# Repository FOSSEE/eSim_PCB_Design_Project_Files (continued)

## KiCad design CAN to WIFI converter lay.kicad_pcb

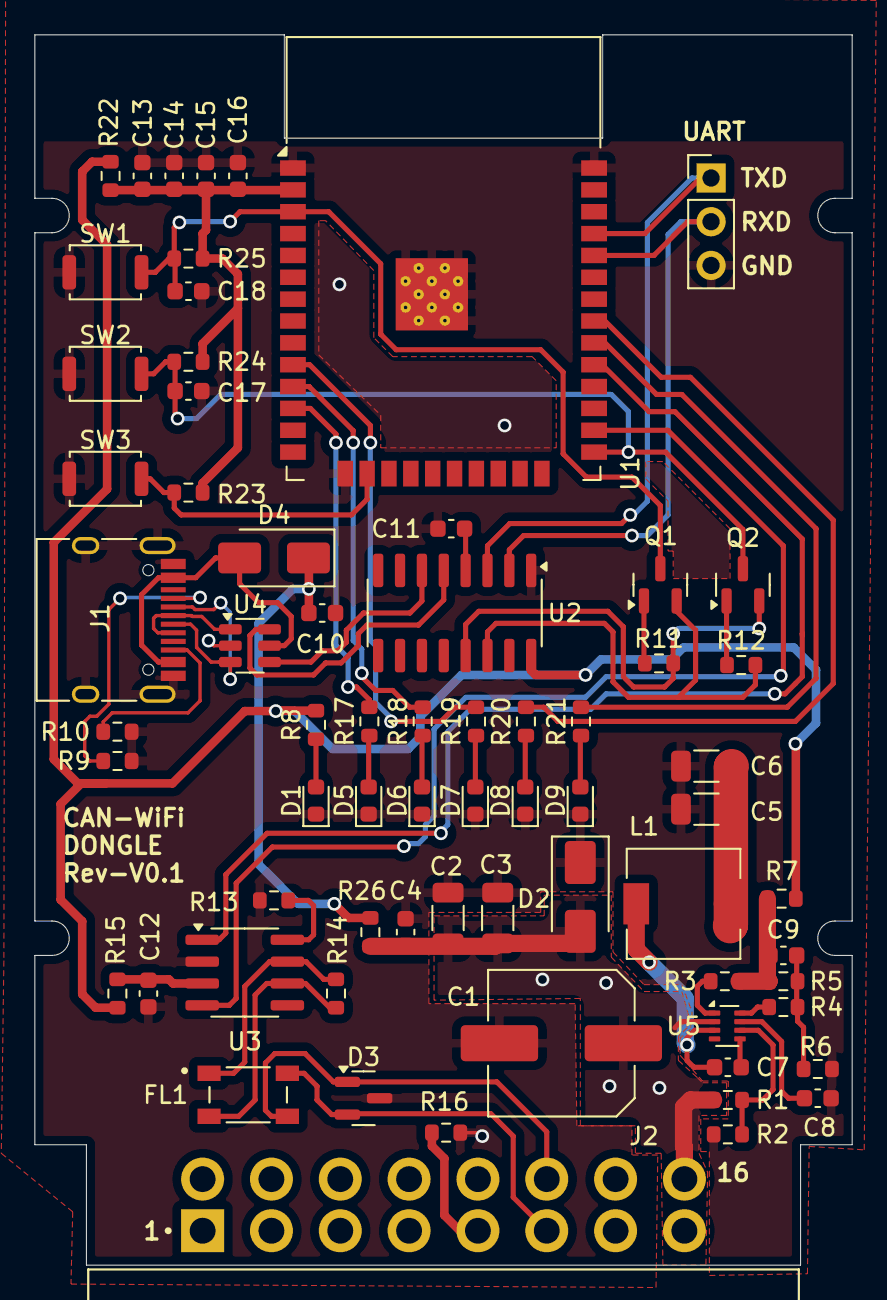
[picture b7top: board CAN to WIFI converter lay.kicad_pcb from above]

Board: 2 copper layers, 47.5 x 71.5 mm, 68 parts (0 on the bottom side), 51 nets.

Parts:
C1: 220uF; C_Elec_8x10.2
C2, C3: 10uF; C_1206_3216Metric
C4, C7, C12, C13, C14, C15, C16, C17, C18: 0.1uF; C_0603_1608Metric
C5, C6: 22uF; C_1206_3216Metric
C8: 22nF; C_0603_1608Metric
C9: 470pF; C_0603_1608Metric
C10: 10uF; C_0603_1608Metric
C11: 10nF; C_0603_1608Metric
D1, D5, D6, D7, D8, D9: LED; LED_0603_1608Metric
D2: SMAJ15CA; D_SMA
D3: SZNUP2105L; SOT-23
D4: SS14; D_SMA
FL1: ACT45B-510-2P-TL003; FIL_ACT45B-510-2P-TL003
J1: USB_C_Receptacle_USB2.0_16P; USB_C_Receptacle_HRO_TYPE-C-31-M-12
J2: C-OBD-II-16M; COMTECH_C-OBD-II-16M
J3: Conn_01x03_Pin; PinHeader_1x03_P2.54mm_Vertical
L1: 6.8uH; L_6.3x6.3_H3
Q1, Q2: SS8050; SOT-23
R1: 191K; R_0603_1608Metric
R2: 49.9K; R_0603_1608Metric
R3: 100K; R_0603_1608Metric
R4, R11, R12, R23, R24, R25: 10K; R_0603_1608Metric
R5: 51K; R_0603_1608Metric
R6: 9.09K; R_0603_1608Metric
R7, R15, R16, R22, R26: 0E; R_0603_1608Metric
R8, R17, R18, R19, R20, R21: 1K; R_0603_1608Metric
R9, R10: 5.1K; R_0603_1608Metric
R13: 2.4K; R_0603_1608Metric
R14: 120E; R_0603_1608Metric
SW1, SW2, SW3: SW_Push; SW_Push_SPST_NO_Alps_SKRK
U1: ESP32-WROOM-32
U2: CH340C; SOIC-16_3.9x9.9mm_P1.27mm
U3: SN65HVD230; SOIC-8_3.9x4.9mm_P1.27mm
U4: USBLC6-4SC6; SOT-23-6
U5: MP2338GTL-P; SOT-583-8

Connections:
5V: C10.1, D4.1 (K), R26.1
+3.3V: R7.1, R8.2, R15.2, R22.2, U2.16 (VCC)
BT/LED/IO25: R19.2, U1.10 (IO25)
CAN_3V3: C12.1, R15.1, U3.3 (VCC)
CAN_H: D3.2 (K), FL1.4, J2.6
CAN_L: D3.1 (K), FL1.3, J2.14
CAN_RX: U1.26 (IO4), U3.4 (R)
CAN_TX: U1.29 (IO5), U3.1 (D)
COMM/LED/IO18: R21.2, U1.30 (IO18)
D+: U2.5 (UD+), U4.6 (I/O4)
D-: U2.6 (UD-), U4.4 (I/O3)
DTR: Q2.2 (E), R11.2, U2.13 (~DTR)
EN: C18.2, Q1.3 (C), R25.1, SW1.2, U1.3 (EN)
ESP_3V3: C13.1, C14.1, C15.1, C16.1, R22.1, R23.2, R24.2, R25.2, U1.2 (VDD)
EXTRA/LED/IO19: R20.2, U1.31 (IO19)
EXT_GND: J2.5, R16.2
FAULT/LED/IO27: R17.2, U1.12 (IO27)
GND: C1.2, C2.2, C3.2, C4.2, C5.2, C6.2, C8.2, C10.2, C11.1, C12.2, C13.2, C14.2, C15.2, C16.2, C17.1, C18.1, D1.1 (K), D2.1 (A1), D3.3 (A), D5.1 (K), D6.1 (K), D7.1 (K), D8.1 (K), D9.1 (K), J1.A1 (GND), J1.A12 (GND), J1.B1 (GND), J1.B12 (GND), J1.S1 (SHIELD), J3.3, R2.2, R6.1, R9.1, R10.1, R13.2, R16.1, SW1.1, SW2.1, SW3.1, U1.1 (GND), U1.15 (GND), U1.38 (GND), U1.39 (GND), U2.1 (GND), U3.2 (GND), U4.2 (GND), U5.4 (GND)
IO0: C17.2, Q2.3 (C), R24.1, SW2.2, U1.25 (IO0)
unnamed: C5.1, C6.1, L1.2
unnamed: C9.2, R4.2, R5.1, R6.2
unnamed: D1.2 (A), R8.1
unnamed: D5.2 (A), R17.1
unnamed: D6.2 (A), R18.1
unnamed: D7.2 (A), R19.1
unnamed: D8.2 (A), R20.1
unnamed: D9.2 (A), R21.1
unnamed: J1.A5 (CC1), R9.2
unnamed: J1.B5 (CC2), R10.2
unnamed: Q1.1 (B), R11.1
unnamed: Q2.1 (B), R12.1
unnamed: C11.2, U2.4 (V3)
unnamed: FL1.1, R14.1, U3.7 (CANH)
unnamed: FL1.2, R14.2, U3.6 (CANL)
unnamed: R13.1, U3.8 (Rs)
unnamed: C7.2, U5.5 (BST)
unnamed: R4.1, U5.8 (FB)
unnamed: R3.2, U5.1 (PG)
unnamed: C8.1, U5.7 (SS)
unnamed: C7.1, L1.1, U5.3 (SW)
P_EN: R1.2, R2.1, U5.6 (EN)
RTS: Q1.2 (E), R12.2, U2.14 (~RTS)
RXD: J3.2, U1.34 (RXD0/IO3), U2.2 (TXD)
SW1/IO13: R23.1, SW3.2, U1.16 (IO13)
TXD: J3.1, U1.35 (TXD0/IO1), U2.3 (RXD)
USB_D+: J1.A6 (D+), J1.B6 (D+), U4.1 (I/O1)
USB_D-: J1.A7 (D-), J1.B7 (D-), U4.3 (I/O2)
VOUT: C9.1, R3.1, R5.2, R7.2
V_BATT: C1.1, C2.1, C3.1, C4.1, D2.2 (A2), J2.16, R1.1, R26.2, U5.2 (VIN)
V_BUS: D4.2 (A), J1.A4 (VBUS), J1.A9 (VBUS), J1.B4 (VBUS), J1.B9 (VBUS), U4.5 (VBUS)
WIFI/LED/IO26: R18.2, U1.11 (IO26)

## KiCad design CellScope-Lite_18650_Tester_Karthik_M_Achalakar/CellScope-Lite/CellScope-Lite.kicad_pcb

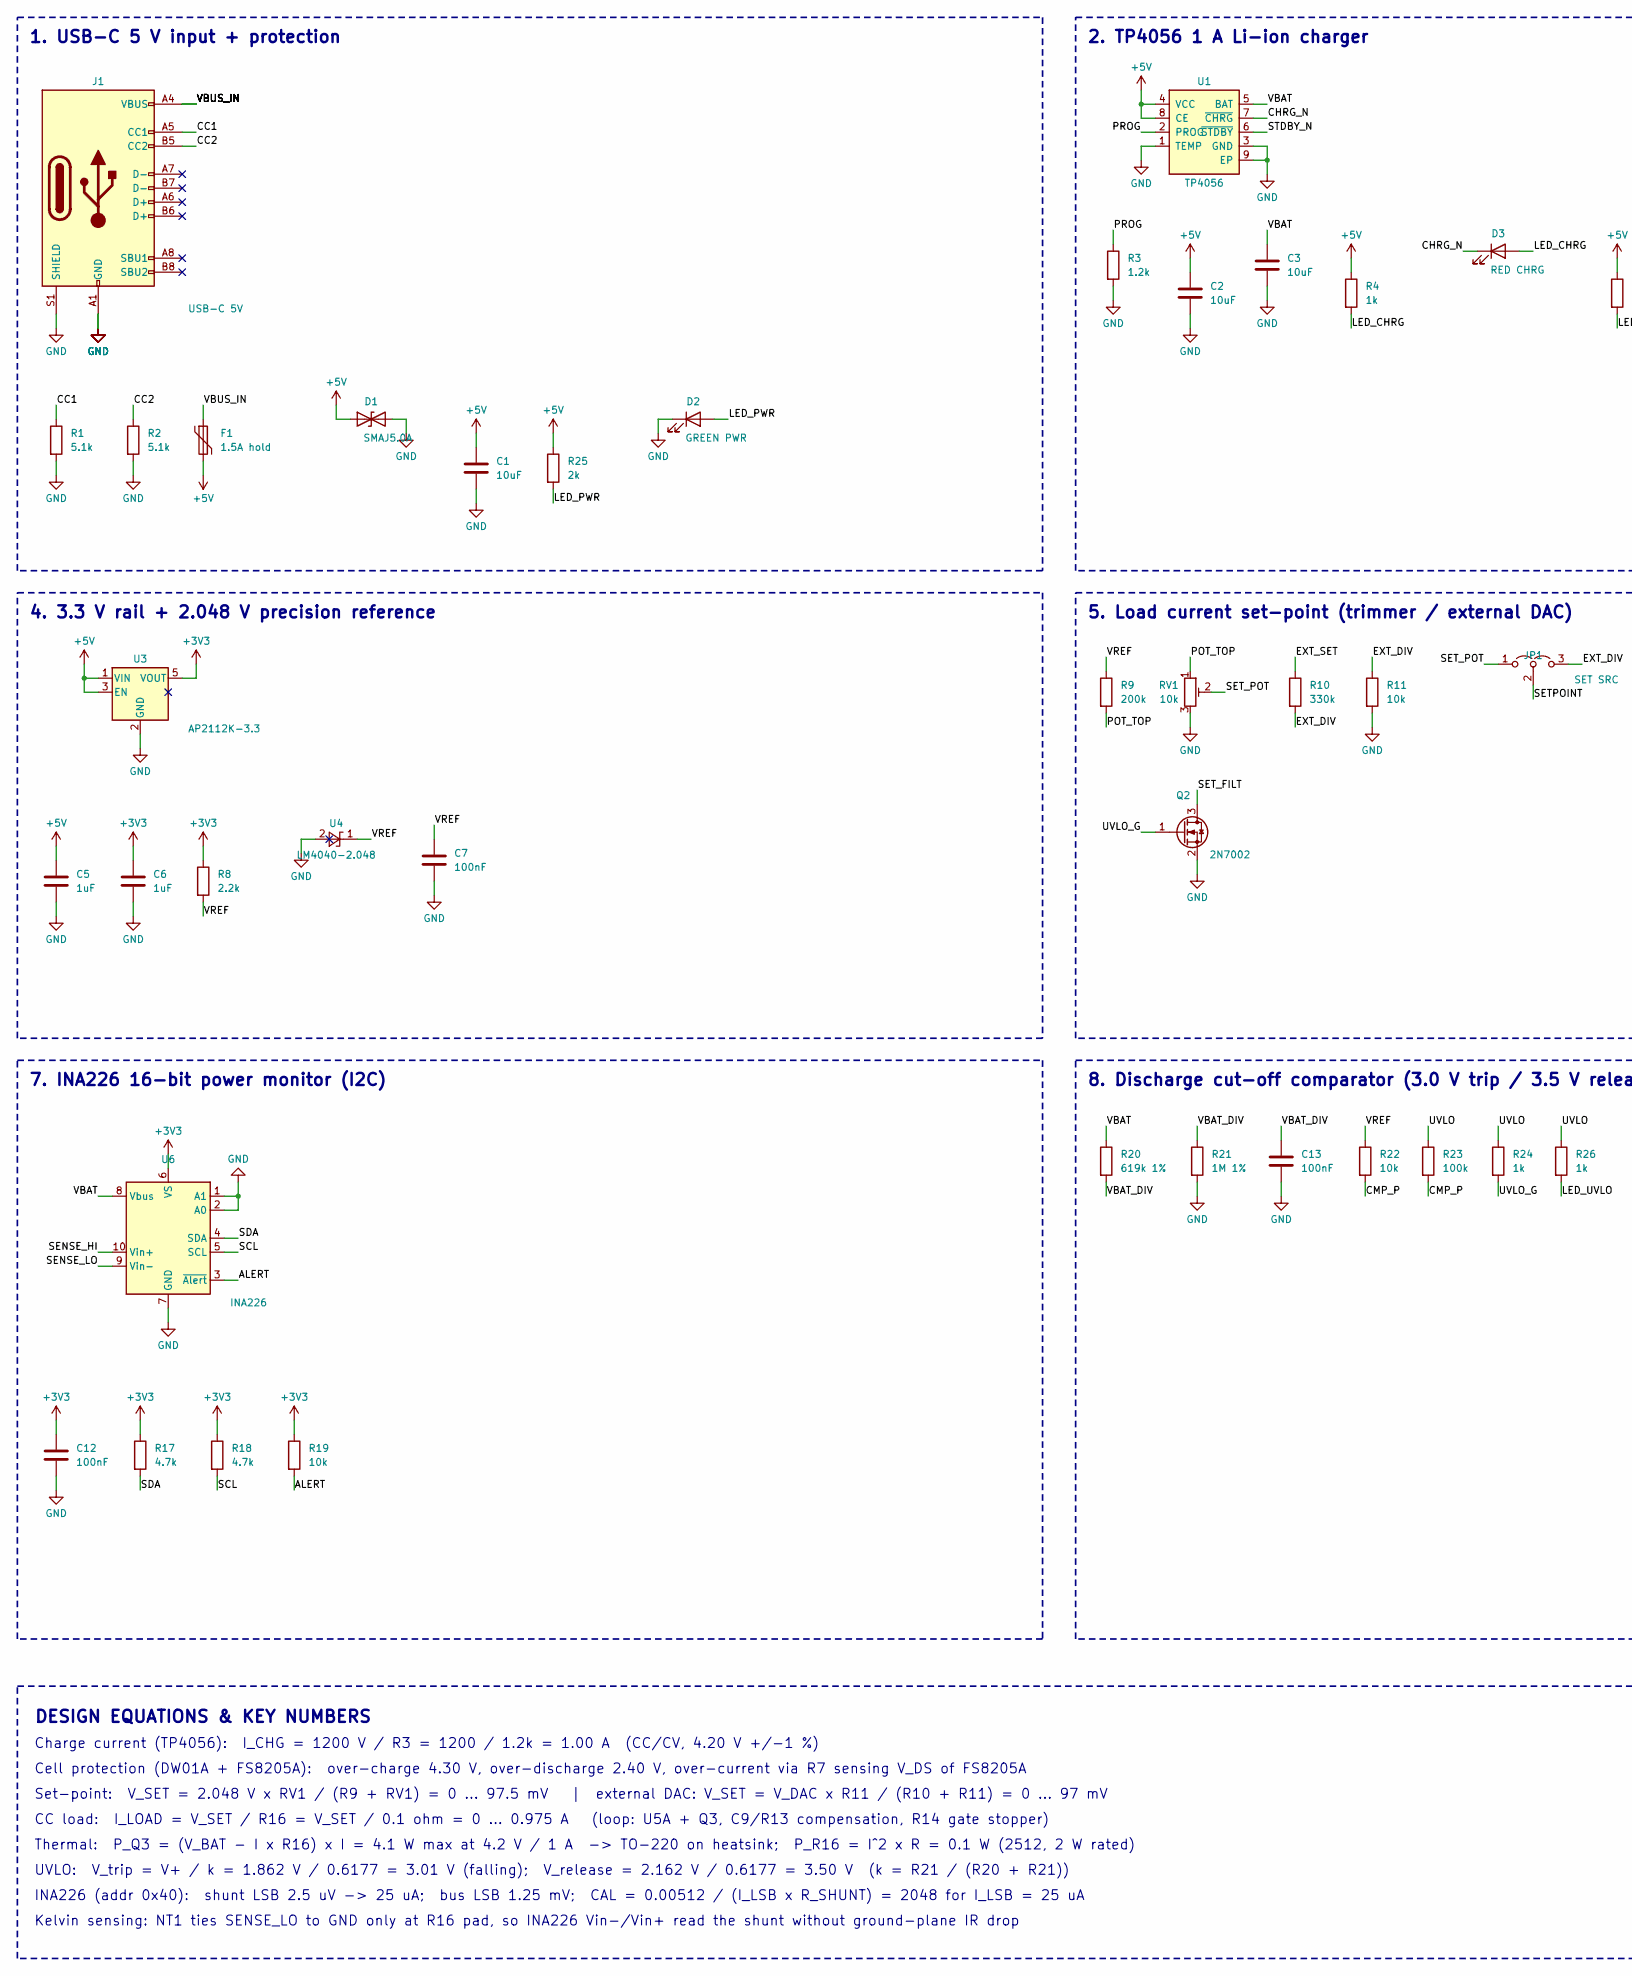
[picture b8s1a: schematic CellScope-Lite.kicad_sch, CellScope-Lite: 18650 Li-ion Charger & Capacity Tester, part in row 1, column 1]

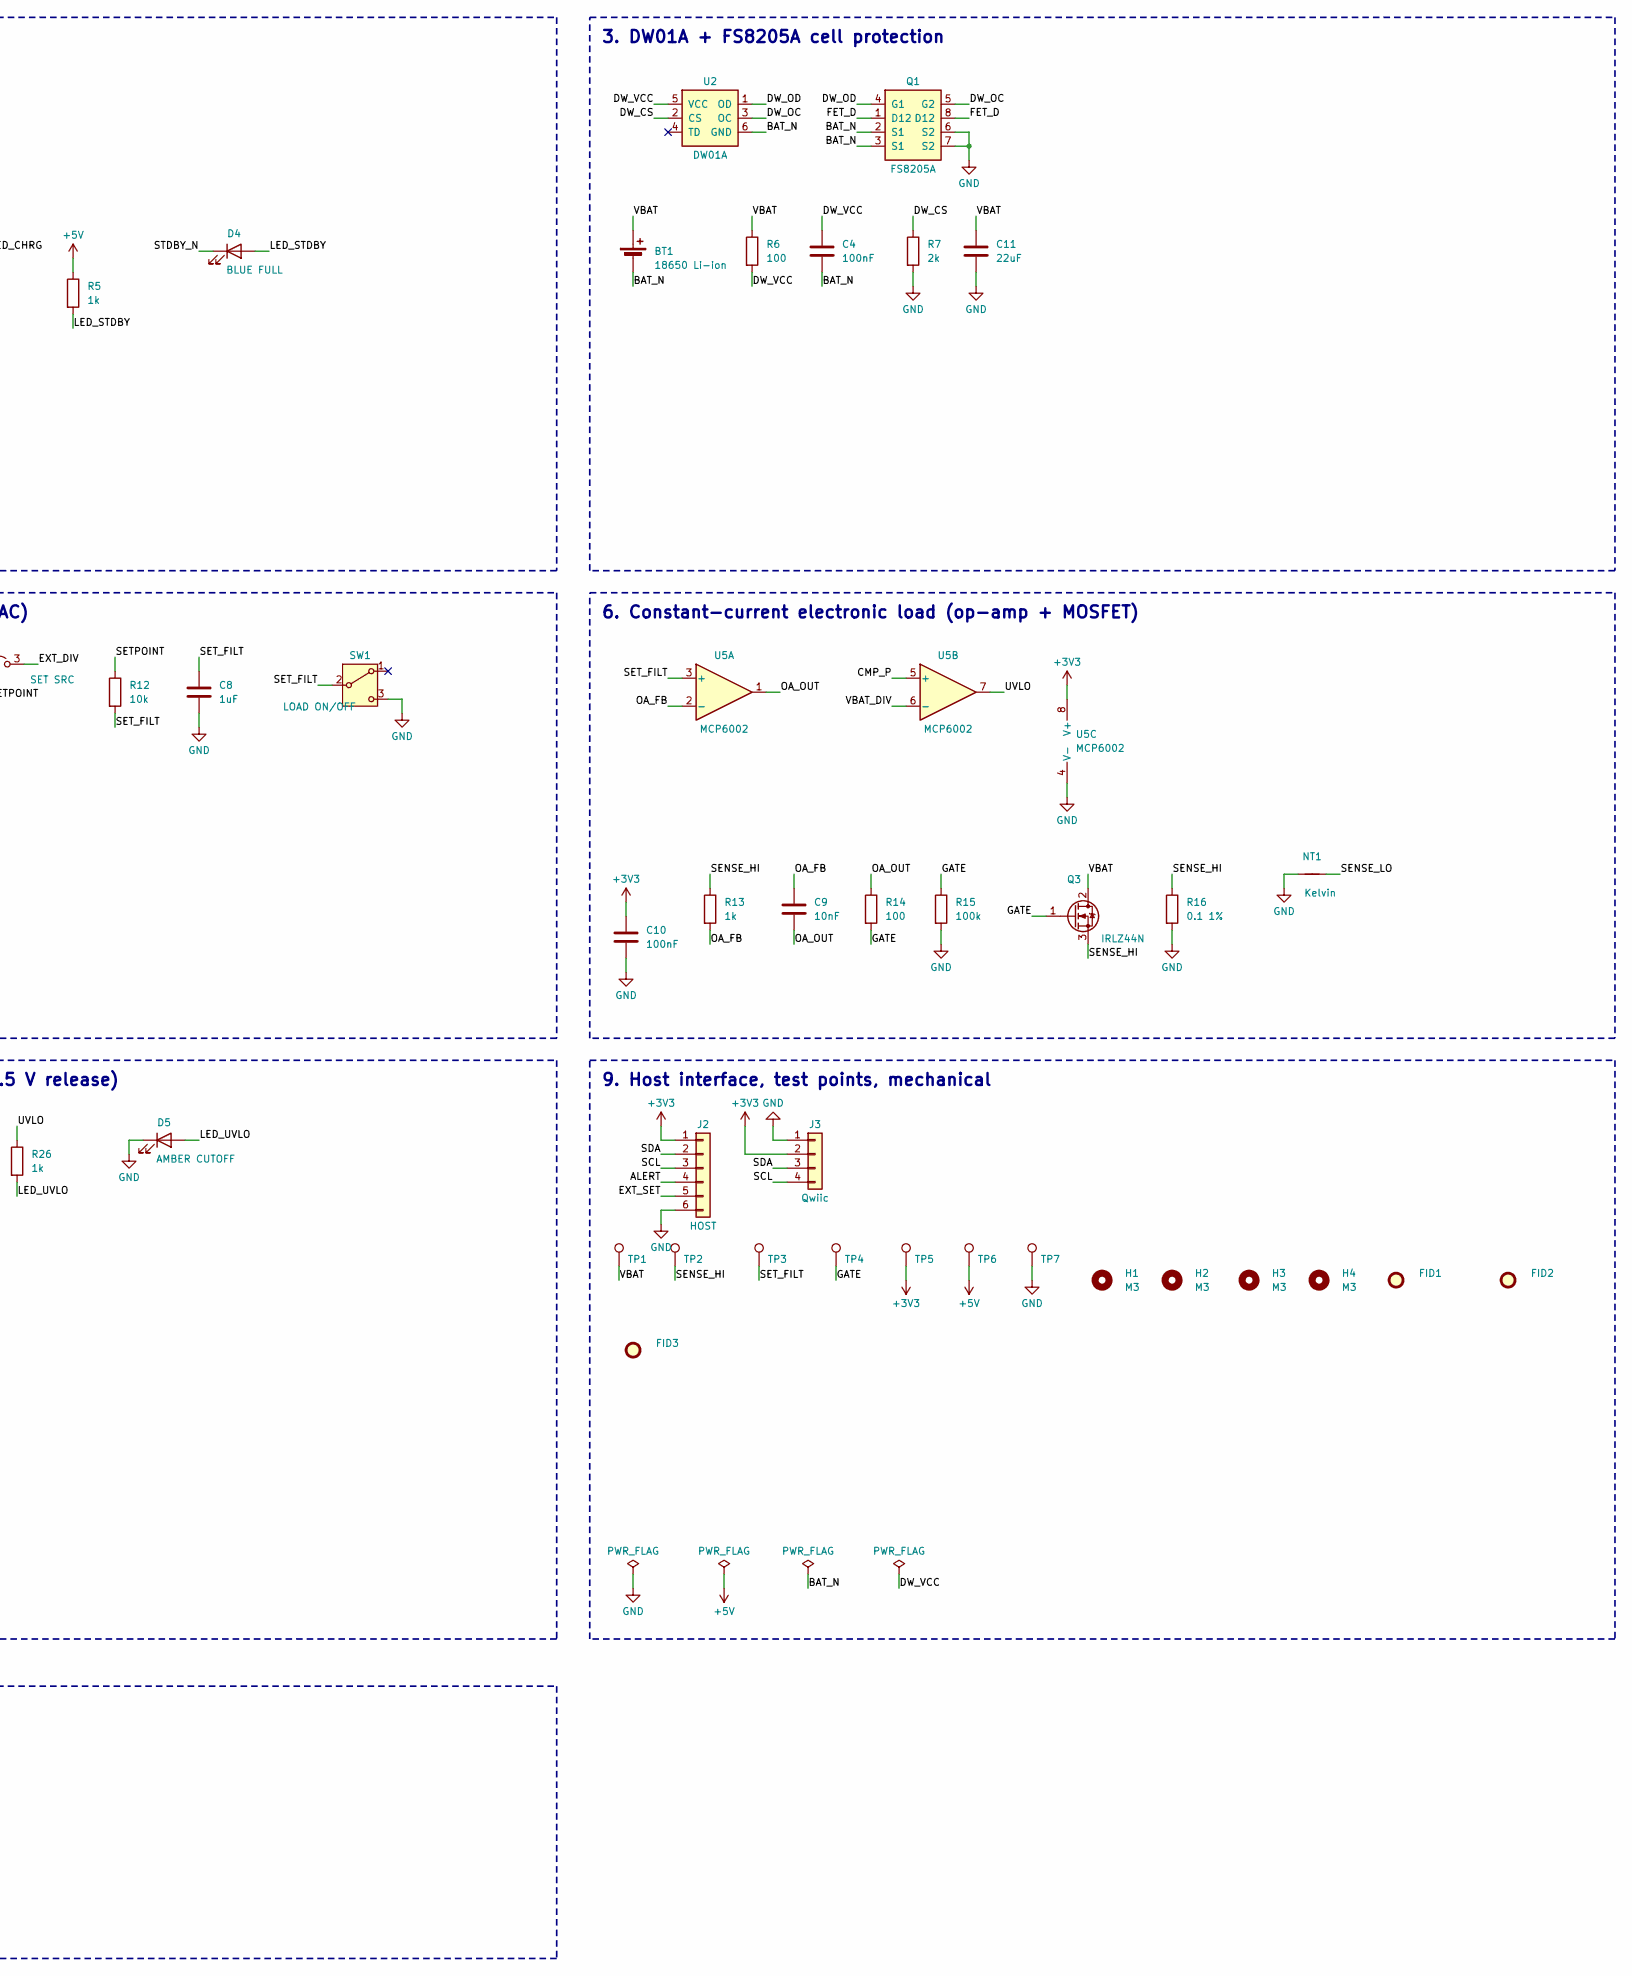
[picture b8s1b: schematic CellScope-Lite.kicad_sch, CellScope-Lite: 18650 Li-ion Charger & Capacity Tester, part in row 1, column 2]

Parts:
BT1: 18650 Li-ion; BatteryHolder_Keystone_1042_1x18650; MPN Keystone 1042
C1, C2, C3: 10uF; C_0805_2012Metric
C4, C7, C10, C12, C13: 100nF; C_0603_1608Metric
C5, C6, C8: 1uF; C_0603_1608Metric
C9: 10nF; C_0603_1608Metric
C11: 22uF; C_0805_2012Metric
D1: SMAJ5.0A; D_SMA; MPN SMAJ5.0A
D2: GREEN PWR; LED_0603_1608Metric
D3: RED CHRG; LED_0603_1608Metric
D4: BLUE FULL; LED_0603_1608Metric
D5: AMBER CUTOFF; LED_0603_1608Metric
F1: 1.5A hold; Fuse_1206_3216Metric; MPN SMD1206P150TF
FID1, FID2, FID3: Fiducial; Fiducial_1mm_Mask2mm
H1, H2, H3, H4: M3; MountingHole_3.2mm_M3
J1: USB-C 5V; USB_C_Receptacle_HRO_TYPE-C-31-M-12; MPN HRO TYPE-C-31-M-12; LCSC C165948
J2: HOST; PinHeader_1x06_P2.54mm_Vertical
J3: Qwiic; JST_SH_SM04B-SRSS-TB_1x04-1MP_P1.00mm_Horizontal; MPN JST SM04B-SRSS-TB
JP1: SET SRC; PinHeader_1x03_P2.54mm_Vertical
NT1: Kelvin; NetTie-2_SMD_Pad0.5mm
Q1: FS8205A; TSSOP-8_4.4x3mm_P0.65mm; MPN FS8205A; LCSC C32254
Q2: 2N7002; SOT-23; LCSC C8545
Q3: IRLZ44N; TO-220-3_Vertical; MPN IRLZ44NPBF
R1, R2: 5.1k; R_0603_1608Metric
R3: 1.2k; R_0603_1608Metric
R4, R5, R13, R24, R26: 1k; R_0603_1608Metric
R6, R14: 100; R_0603_1608Metric
R7, R25: 2k; R_0603_1608Metric
R8: 2.2k; R_0603_1608Metric
R9: 200k; R_0603_1608Metric
R10: 330k; R_0603_1608Metric
R11, R12, R19, R22: 10k; R_0603_1608Metric
R15, R23: 100k; R_0603_1608Metric
R16: 0.1 1%; R_2512_6332Metric; MPN 2512 0.1R 1% 2W
R17, R18: 4.7k; R_0603_1608Metric
R20: 619k 1%; R_0603_1608Metric
R21: 1M 1%; R_0603_1608Metric
RV1: 10k; Potentiometer_Bourns_3296W_Vertical; MPN Bourns 3296W-1-103
SW1: LOAD ON/OFF; SW_SPDT_PCM12; MPN C&K PCM12SMTR
TP1: VBAT; TestPoint_Pad_D1.5mm
TP2: SENSE_HI; TestPoint_Pad_D1.5mm
TP3: SET_FILT; TestPoint_Pad_D1.5mm
TP4: GATE; TestPoint_Pad_D1.5mm
TP5: 3V3; TestPoint_Pad_D1.5mm
TP6: 5V; TestPoint_Pad_D1.5mm
TP7: GND; TestPoint_Pad_D1.5mm
U1: TP4056; SOIC-8-1EP_3.9x4.9mm_P1.27mm_EP2.29x3mm; MPN TP4056 (ESOP-8); LCSC C16581
U2: DW01A; SOT-23-6; MPN DW01A; LCSC C351410
U3: AP2112K-3.3; SOT-23-5; MPN AP2112K-3.3TRG1; LCSC C51118
U4: LM4040-2.048; SOT-23; MPN LM4040AIM3-2.0
U5: MCP6002; SOIC-8_3.9x4.9mm_P1.27mm; MPN MCP6002T-I/SN
U6: INA226; MSOP-10_3x3mm_P0.5mm; MPN INA226AIDGSR; LCSC C49851

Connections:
+3V3: C6.1, C10.1, C12.1, J2.1, J3.2, R8.1, R17.1, R18.1, R19.1, TP5.1, U3.5 (VOUT), U5.8 (V+), U6.6 (VS)
+5V: C1.1, C2.1, C5.1, D1.1 (A1), F1.2, R4.1, R5.1, R25.1, TP6.1, U1.4 (VCC), U1.8 (CE), U3.1 (VIN), U3.3 (EN)
/ALERT: J2.4, R19.2, U6.3 (~Alert)
/BAT_N: BT1.2 (-), C4.2, Q1.2 (S1), Q1.3 (S1), U2.6 (GND)
/CC1: J1.A5 (CC1), R1.1
/CC2: J1.B5 (CC2), R2.1
/CHRG_N: D3.1 (K), U1.7 (~CHRG)
/CMP_P: R22.2, R23.2, U5.5 (+)
/DW_CS: R7.1, U2.2 (CS)
/DW_OC: Q1.5 (G2), U2.3 (OC)
/DW_OD: Q1.4 (G1), U2.1 (OD)
/DW_VCC: C4.1, R6.2, U2.5 (VCC)
/EXT_DIV: JP1.3 (B), R10.2, R11.1
/EXT_SET: J2.5, R10.1
/FET_D: Q1.1 (D12), Q1.8 (D12)
/GATE: Q3.1 (G), R14.2, R15.1, TP4.1
/LED_CHRG: D3.2 (A), R4.2
/LED_PWR: D2.2 (A), R25.2
/LED_STDBY: D4.2 (A), R5.2
/LED_UVLO: D5.2 (A), R26.2
/OA_FB: C9.1, R13.2, U5.2 (-)
/OA_OUT: C9.2, R14.1, U5.1
/POT_TOP: R9.2, RV1.1
/PROG: R3.1, U1.2 (PROG)
/SCL: J2.3, J3.4, R18.2, U6.5 (SCL)
/SDA: J2.2, J3.3, R17.2, U6.4 (SDA)
/SENSE_HI: Q3.3 (S), R13.1, R16.1, TP2.1, U6.10 (Vin+)
/SENSE_LO: NT1.2, U6.9 (Vin-)
/SETPOINT: JP1.2 (C), R12.1
/SET_FILT: C8.1, Q2.3 (D), R12.2, SW1.2 (B), TP3.1, U5.3 (+)
/SET_POT: JP1.1 (A), RV1.2
/STDBY_N: D4.1 (K), U1.6 (~STDBY)
/UVLO: R23.1, R24.1, R26.1, U5.7
/UVLO_G: Q2.1 (G), R24.2
/VBAT: BT1.1 (+), C3.1, C11.1, Q3.2 (D), R6.1, R20.1, TP1.1, U1.5 (BAT), U6.8 (Vbus)
/VBAT_DIV: C13.1, R20.2, R21.1, U5.6 (-)
/VBUS_IN: F1.1, J1.A4 (VBUS), J1.A9 (VBUS), J1.B4 (VBUS), J1.B9 (VBUS)
/VREF: C7.1, R8.2, R9.1, R22.1, U4.1 (K)
GND: C1.2, C2.2, C3.2, C5.2, C6.2, C7.2, C8.2, C10.2, C11.2, C12.2, C13.2, D1.2 (A2), D2.1 (K), D5.1 (K), J1.A1 (GND), J1.A12 (GND), J1.B1 (GND), J1.B12 (GND), J1.S1 (SHIELD), J2.6, J3.1, NT1.1, Q1.6 (S2), Q1.7 (S2), Q2.2 (S), R1.2, R2.2, R3.2, R7.2, R11.2, R15.2, R16.2, R21.2, RV1.3, SW1.3 (C), TP7.1, U1.1 (TEMP), U1.3 (GND), U1.9 (EP), U3.2 (GND), U4.2 (A), U5.4 (V-), U6.1 (A1), U6.2 (A0), U6.7 (GND)

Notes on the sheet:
1. USB-C 5 V input + protection
2. TP4056 1 A Li-ion charger
3. DW01A + FS8205A cell protection
4. 3.3 V rail + 2.048 V precision reference
5. Load current set-point (trimmer / external DAC)
6. Constant-current electronic load (op-amp + MOSFET)
7. INA226 16-bit power monitor (I2C)
8. Discharge cut-off comparator (3.0 V trip / 3.5 V release)
9. Host interface, test points, mechanical
DESIGN EQUATIONS & KEY NUMBERS
Charge current (TP4056): I_CHG = 1200 V / R3 = 1200 / 1.2k = 1.00 A (CC/CV, 4.20 V +/-1 %)
Cell protection (DW01A + FS8205A): over-charge 4.30 V, over-discharge 2.40 V, over-current via R7 sensing V_DS of FS8205A
Set-point: V_SET = 2.048 V x RV1 / (R9 + RV1) = 0 ... 97.5 mV | external DAC: V_SET = V_DAC x R11 / (R10 + R11) = 0 ... 97 mV
CC load: I_LOAD = V_SET / R16 = V_SET / 0.1 ohm = 0 ... 0.975 A (loop: U5A + Q3, C9/R13 compensation, R14 gate stopper)
Thermal: P_Q3 = (V_BAT - I x R16) x I = 4.1 W max at 4.2 V / 1 A -> TO-220 on heatsink; P_R16 = I^2 x R = 0.1 W (2512, 2 W rated)
UVLO: V_trip = V+ / k = 1.862 V / 0.6177 = 3.01 V (falling); V_release = 2.162 V / 0.6177 = 3.50 V (k = R21 / (R20 + R21))
INA226 (addr 0x40): shunt LSB 2.5 uV -> 25 uA; bus LSB 1.25 mV; CAL = 0.00512 / (I_LSB x R_SHUNT) = 2048 for I_LSB = 25 uA
Kelvin sensing: NT1 ties SENSE_LO to GND only at R16 pad, so INA226 Vin-/Vin+ read the shunt without ground-plane IR drop

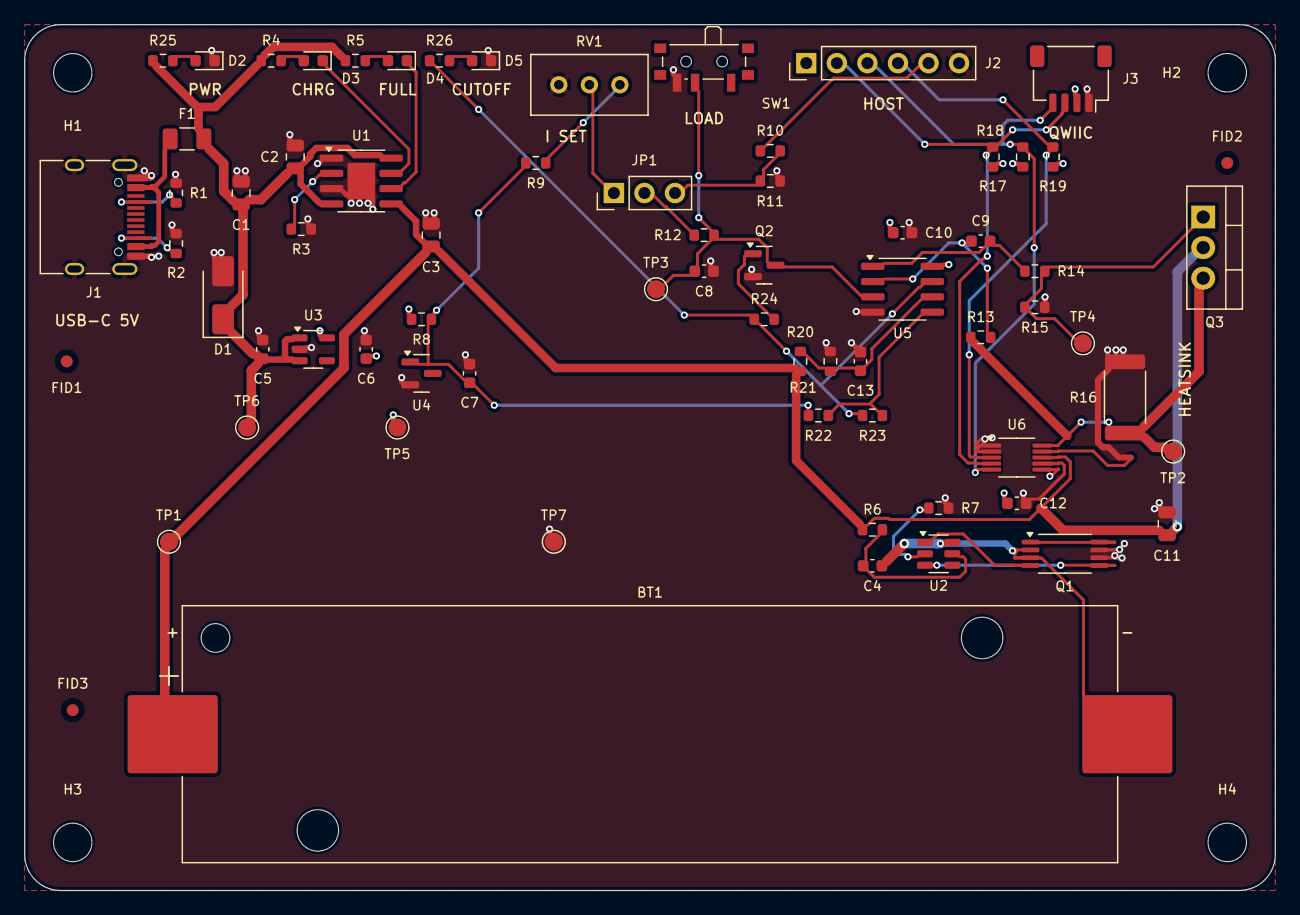
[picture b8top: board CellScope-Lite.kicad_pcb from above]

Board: 4 copper layers, 104.0 x 72.0 mm, 76 parts (0 on the bottom side), 39 nets.

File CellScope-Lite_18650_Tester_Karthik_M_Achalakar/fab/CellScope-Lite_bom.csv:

"Designator","Value","Footprint","MPN","LCSC","Qty"
"BT1","18650 Li-ion","Battery:BatteryHolder_Keystone_1042_1x18650","Keystone 1042","","1"
"C1-C3","10uF","Capacitor_SMD:C_0805_2012Metric","","","3"
"C4,C7,C10,C12,C13","100nF","Capacitor_SMD:C_0603_1608Metric","","","5"
"C5,C6,C8","1uF","Capacitor_SMD:C_0603_1608Metric","","","3"
"C9","10nF","Capacitor_SMD:C_0603_1608Metric","","","1"
"C11","22uF","Capacitor_SMD:C_0805_2012Metric","","","1"
"D1","SMAJ5.0A","Diode_SMD:D_SMA","SMAJ5.0A","","1"
"D2","GREEN PWR","LED_SMD:LED_0603_1608Metric","","","1"
"D3","RED CHRG","LED_SMD:LED_0603_1608Metric","","","1"
"D4","BLUE FULL","LED_SMD:LED_0603_1608Metric","","","1"
"D5","AMBER CUTOFF","LED_SMD:LED_0603_1608Metric","","","1"
"F1","1.5A hold","Fuse:Fuse_1206_3216Metric","SMD1206P150TF","","1"
"J1","USB-C 5V","Connector_USB:USB_C_Receptacle_HRO_TYPE-C-31-M-12","HRO TYPE-C-31-M-12","C165948","1"
"J2","HOST","Connector_PinHeader_2.54mm:PinHeader_1x06_P2.54mm_Vertical","","","1"
"J3","Qwiic","Connector_JST:JST_SH_SM04B-SRSS-TB_1x04-1MP_P1.00mm_Horizontal","JST SM04B-SRSS-TB","","1"
"JP1","SET SRC","Connector_PinHeader_2.54mm:PinHeader_1x03_P2.54mm_Vertical","","","1"
"Q1","FS8205A","Package_SO:TSSOP-8_4.4x3mm_P0.65mm","FS8205A","C32254","1"
"Q2","2N7002","Package_TO_SOT_SMD:SOT-23","","C8545","1"
"Q3","IRLZ44N","Package_TO_SOT_THT:TO-220-3_Vertical","IRLZ44NPBF","","1"
"R1,R2","5.1k","Resistor_SMD:R_0603_1608Metric","","","2"
"R3","1.2k","Resistor_SMD:R_0603_1608Metric","","","1"
"R4,R5,R13,R24,R26","1k","Resistor_SMD:R_0603_1608Metric","","","5"
"R6,R14","100","Resistor_SMD:R_0603_1608Metric","","","2"
"R7,R25","2k","Resistor_SMD:R_0603_1608Metric","","","2"
"R8","2.2k","Resistor_SMD:R_0603_1608Metric","","","1"
"R9","200k","Resistor_SMD:R_0603_1608Metric","","","1"
"R10","330k","Resistor_SMD:R_0603_1608Metric","","","1"
"R11,R12,R19,R22","10k","Resistor_SMD:R_0603_1608Metric","","","4"
"R15,R23","100k","Resistor_SMD:R_0603_1608Metric","","","2"
"R16","0.1 1%","Resistor_SMD:R_2512_6332Metric","2512 0.1R 1% 2W","","1"
"R17,R18","4.7k","Resistor_SMD:R_0603_1608Metric","","","2"
"R20","619k 1%","Resistor_SMD:R_0603_1608Metric","","","1"
"R21","1M 1%","Resistor_SMD:R_0603_1608Metric","","","1"
"RV1","10k","Potentiometer_THT:Potentiometer_Bourns_3296W_Vertical","Bourns 3296W-1-103","","1"
"SW1","LOAD ON/OFF","Button_Switch_SMD:SW_SPDT_PCM12","C&K PCM12SMTR","","1"
"U1","TP4056","Package_SO:SOIC-8-1EP_3.9x4.9mm_P1.27mm_EP2.29x3mm","TP4056 (ESOP-8)","C16581","1"
"U2","DW01A","Package_TO_SOT_SMD:SOT-23-6","DW01A","C351410","1"
"U3","AP2112K-3.3","Package_TO_SOT_SMD:SOT-23-5","AP2112K-3.3TRG1","C51118","1"
"U4","LM4040-2.048","Package_TO_SOT_SMD:SOT-23","LM4040AIM3-2.0","","1"
"U5","MCP6002","Package_SO:SOIC-8_3.9x4.9mm_P1.27mm","MCP6002T-I/SN","","1"
"U6","INA226","Package_SO:MSOP-10_3x3mm_P0.5mm","INA226AIDGSR","C49851","1"
